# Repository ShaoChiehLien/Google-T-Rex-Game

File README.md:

# Google-T-Rex-Game
Introduction: We developed the Google T-Rex Game which could be played using our customized circuit board. The T-Rex needs to overcome the obstacles by jumping across the cactus or dodging the upcoming crow to keep itself alive. The project could be separated into three parts, main game program, sound generation, and hardware development. In order to display the User Interface, we developed our own library to cooperate with the two-screen Graphic LCD (64+64)x64. It should be noted that STM32f051r8t6 has relative small memories(64 Kbyte flash memory and 8 Kbyte of SRAM), so we mainly use for loop and bit map to reduce the memory usage.

For the main game part, we used our own algorithm to randomly produce three different characters: single cactus, cactus cluster and crow with random distances, which is a significant specialty of this project. By using non-visible simple squares to record the characters' position, we could track if the T-Rec touch the cactus or crow and determine if it is Game Over. At last, we added the bit map of each character on the non-visible simple square to finish the User Interface.

For the sound generation, we used the concept of Digital to Analog Conversion, Timer, and Direct Memory Access to generate certain voltage output. By generating a waveform using the analog output and calculate each note's frequency, we could then produce a sound wave of notes from C, D, E to A and B.

Last but not least, the customized printed circuit board is another specialty of this project. The development board is also acceptable for this project, but the wiring is really a pain in the ass, so we developed the circuit board and soldered the STM32f051r8t6 ourselves. The wiring map and PCB are all provided in the above file.

# Project Video Demostration
https://www.youtube.com/watch?v=Yxi9itDUQOI

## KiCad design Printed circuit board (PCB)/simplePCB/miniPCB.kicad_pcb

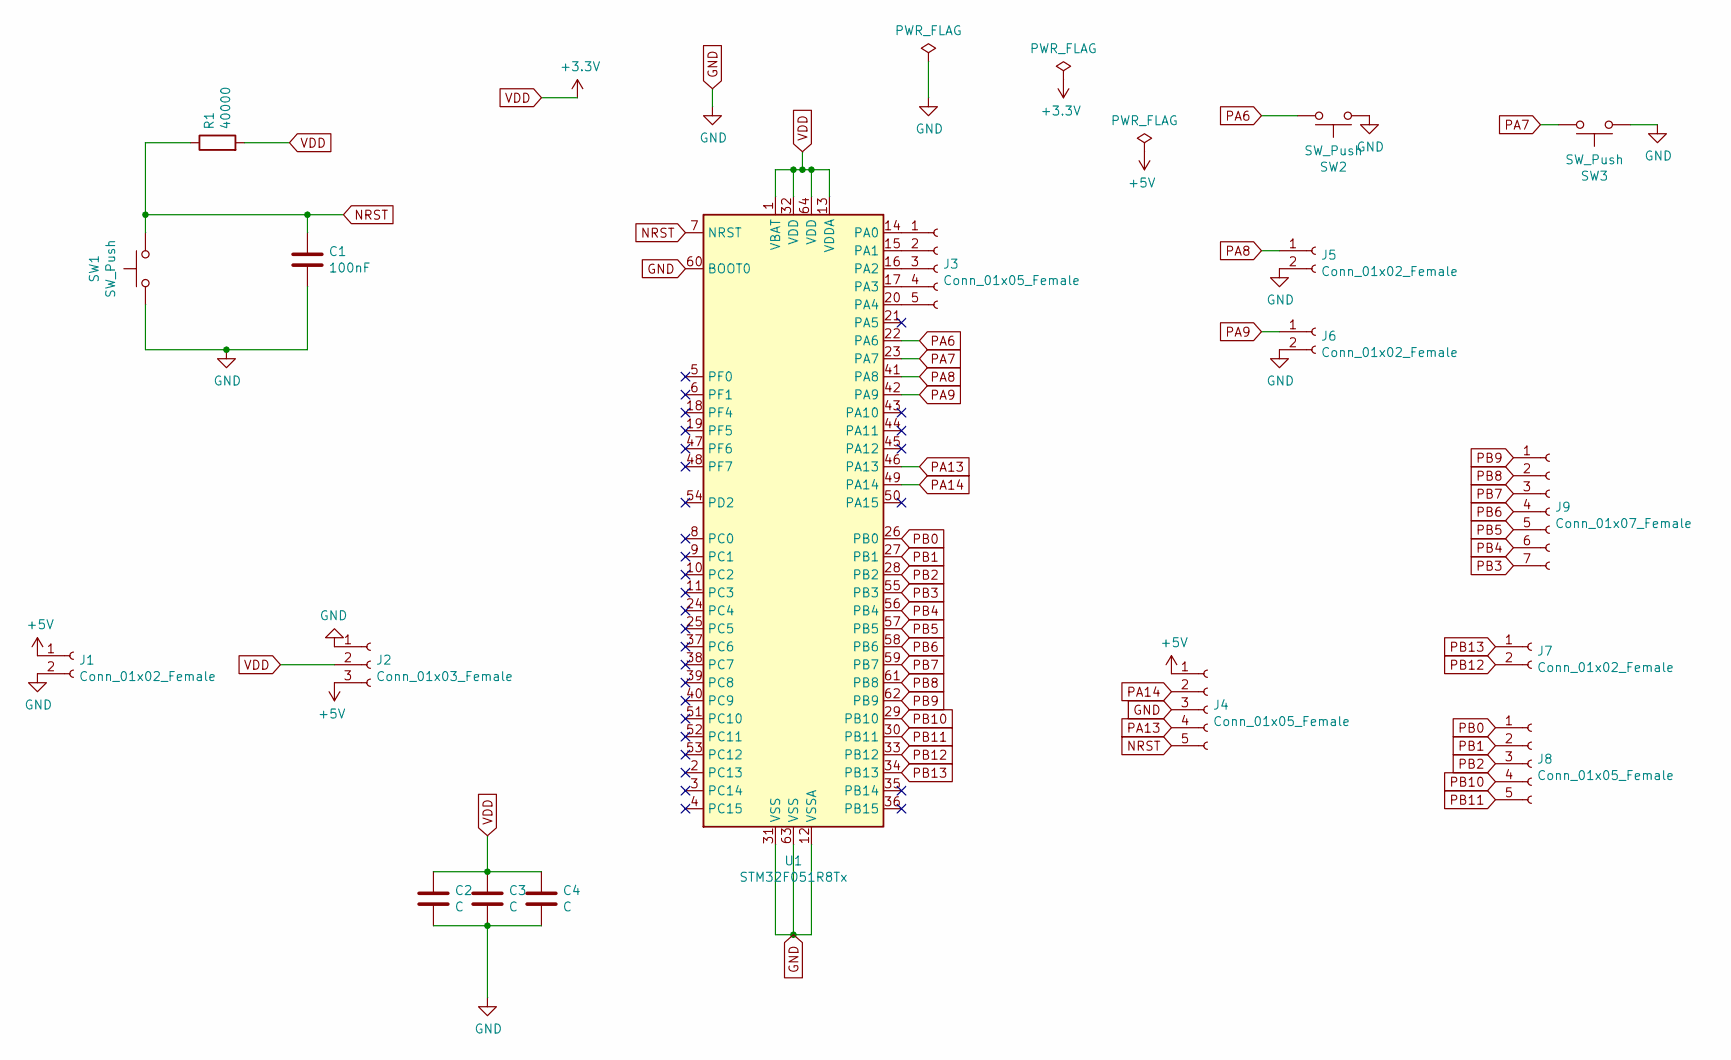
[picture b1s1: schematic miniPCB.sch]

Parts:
C1: 100nF; C_Axial_L3.8mm_D2.6mm_P7.50mm_Horizontal
C2, C3, C4: C; C_Radial_D6.3mm_H5.0mm_P2.50mm
J1, J5, J6, J7: Conn_01x02_Female; PinSocket_1x02_P2.54mm_Vertical
J2: Conn_01x03_Female; PinSocket_1x03_P2.54mm_Vertical
J3, J4, J8: Conn_01x05_Female; PinSocket_1x05_P2.54mm_Vertical
J9: Conn_01x07_Female; PinSocket_1x07_P2.54mm_Vertical
R1: 40000; R_Axial_DIN0207_L6.3mm_D2.5mm_P7.62mm_Horizontal
SW1, SW2, SW3: SW_Push; SW_Tactile_Straight_KSA0Axx1LFTR
U1: STM32F051R8Tx; LQFP-64_10x10mm_P0.5mm

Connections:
+5V: J1.1, J2.3, J4.1
GND: C1.2, C2.2, C3.2, C4.2, J1.2, J2.1, J4.3, J5.2, J6.2, SW1.1, SW2.1, SW3.1, U1.12 (VSSA), U1.31 (VSS), U1.60 (BOOT0), U1.63 (VSS)
NRST: C1.1, J4.5, R1.1, SW1.2, U1.7 (NRST)
unnamed: J3.1, U1.14 (PA0)
unnamed: J3.2, U1.15 (PA1)
unnamed: J3.3, U1.16 (PA2)
unnamed: J3.4, U1.17 (PA3)
unnamed: J3.5, U1.20 (PA4)
PA6: SW2.2, U1.22 (PA6)
PA7: SW3.2, U1.23 (PA7)
PA8: J5.1, U1.41 (PA8)
PA9: J6.1, U1.42 (PA9)
PA13: J4.4, U1.46 (PA13)
PA14: J4.2, U1.49 (PA14)
PB0: J8.1, U1.26 (PB0)
PB1: J8.2, U1.27 (PB1)
PB2: J8.3, U1.28 (PB2)
PB3: J9.7, U1.55 (PB3)
PB4: J9.6, U1.56 (PB4)
PB5: J9.5, U1.57 (PB5)
PB6: J9.4, U1.58 (PB6)
PB7: J9.3, U1.59 (PB7)
PB8: J9.2, U1.61 (PB8)
PB9: J9.1, U1.62 (PB9)
PB10: J8.4, U1.29 (PB10)
PB11: J8.5, U1.30 (PB11)
PB12: J7.2, U1.33 (PB12)
PB13: J7.1, U1.34 (PB13)
VDD: C2.1, C3.1, C4.1, J2.2, R1.2, U1.1 (VBAT), U1.13 (VDDA), U1.32 (VDD), U1.64 (VDD)

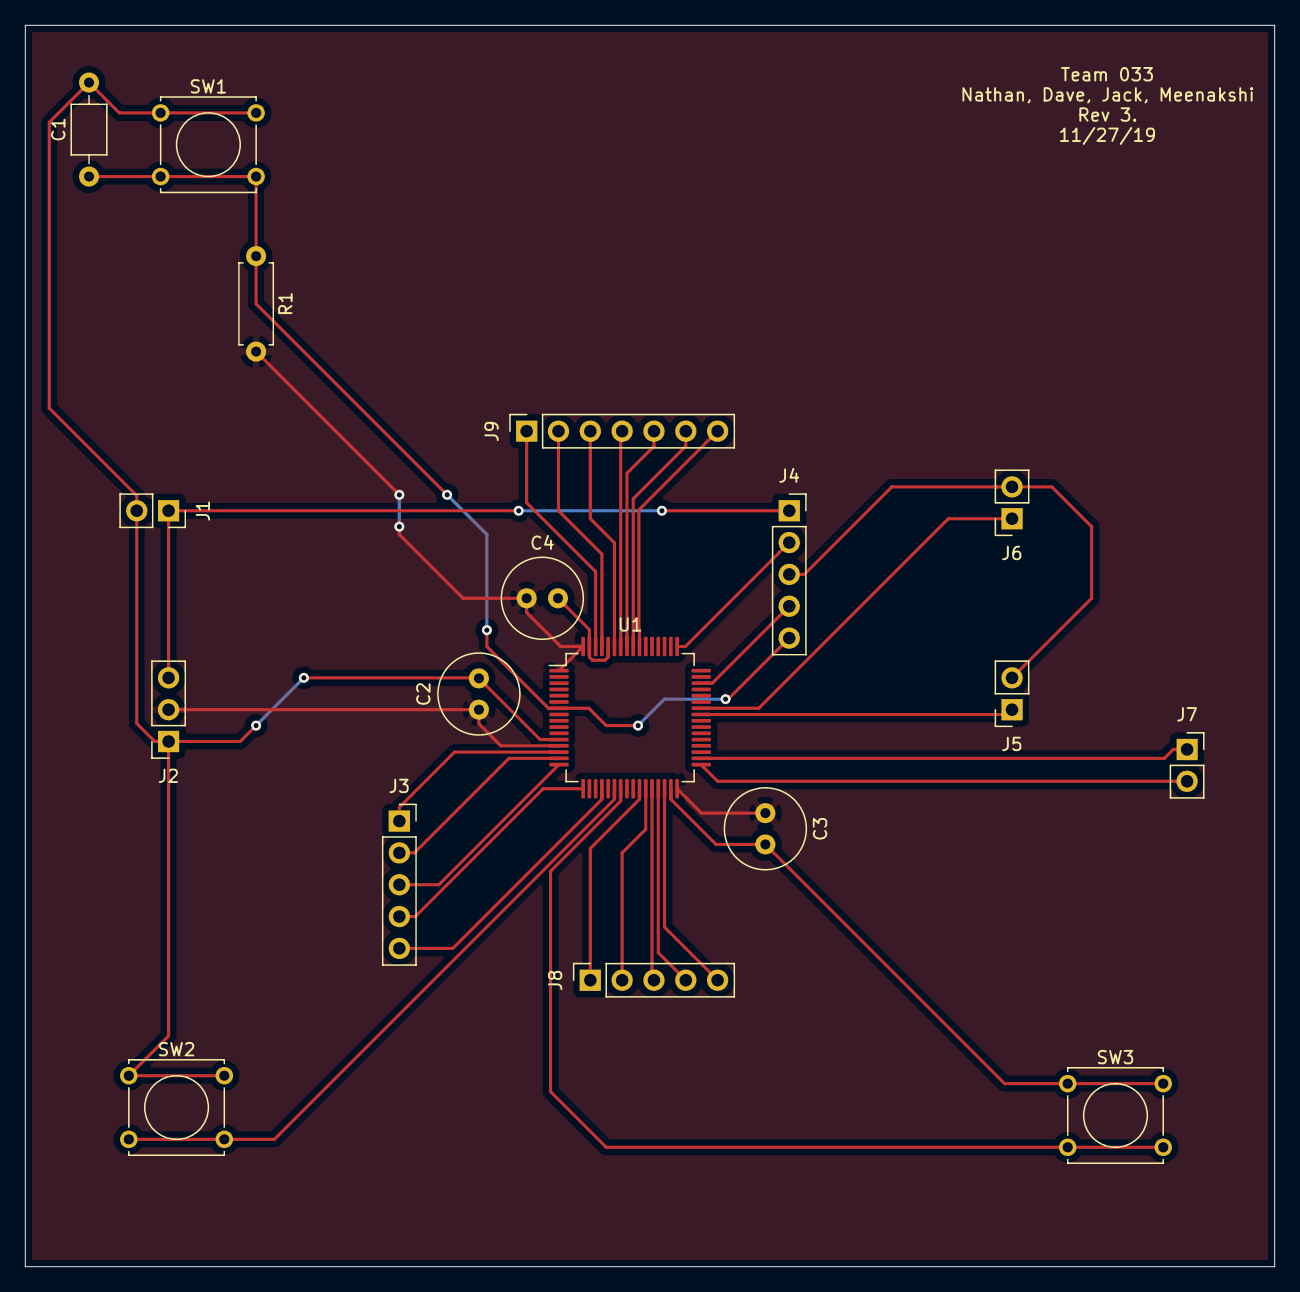
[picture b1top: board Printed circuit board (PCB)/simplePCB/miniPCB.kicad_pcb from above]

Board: 2 copper layers, 99.7 x 99.1 mm, 18 parts (0 on the bottom side), 29 nets.

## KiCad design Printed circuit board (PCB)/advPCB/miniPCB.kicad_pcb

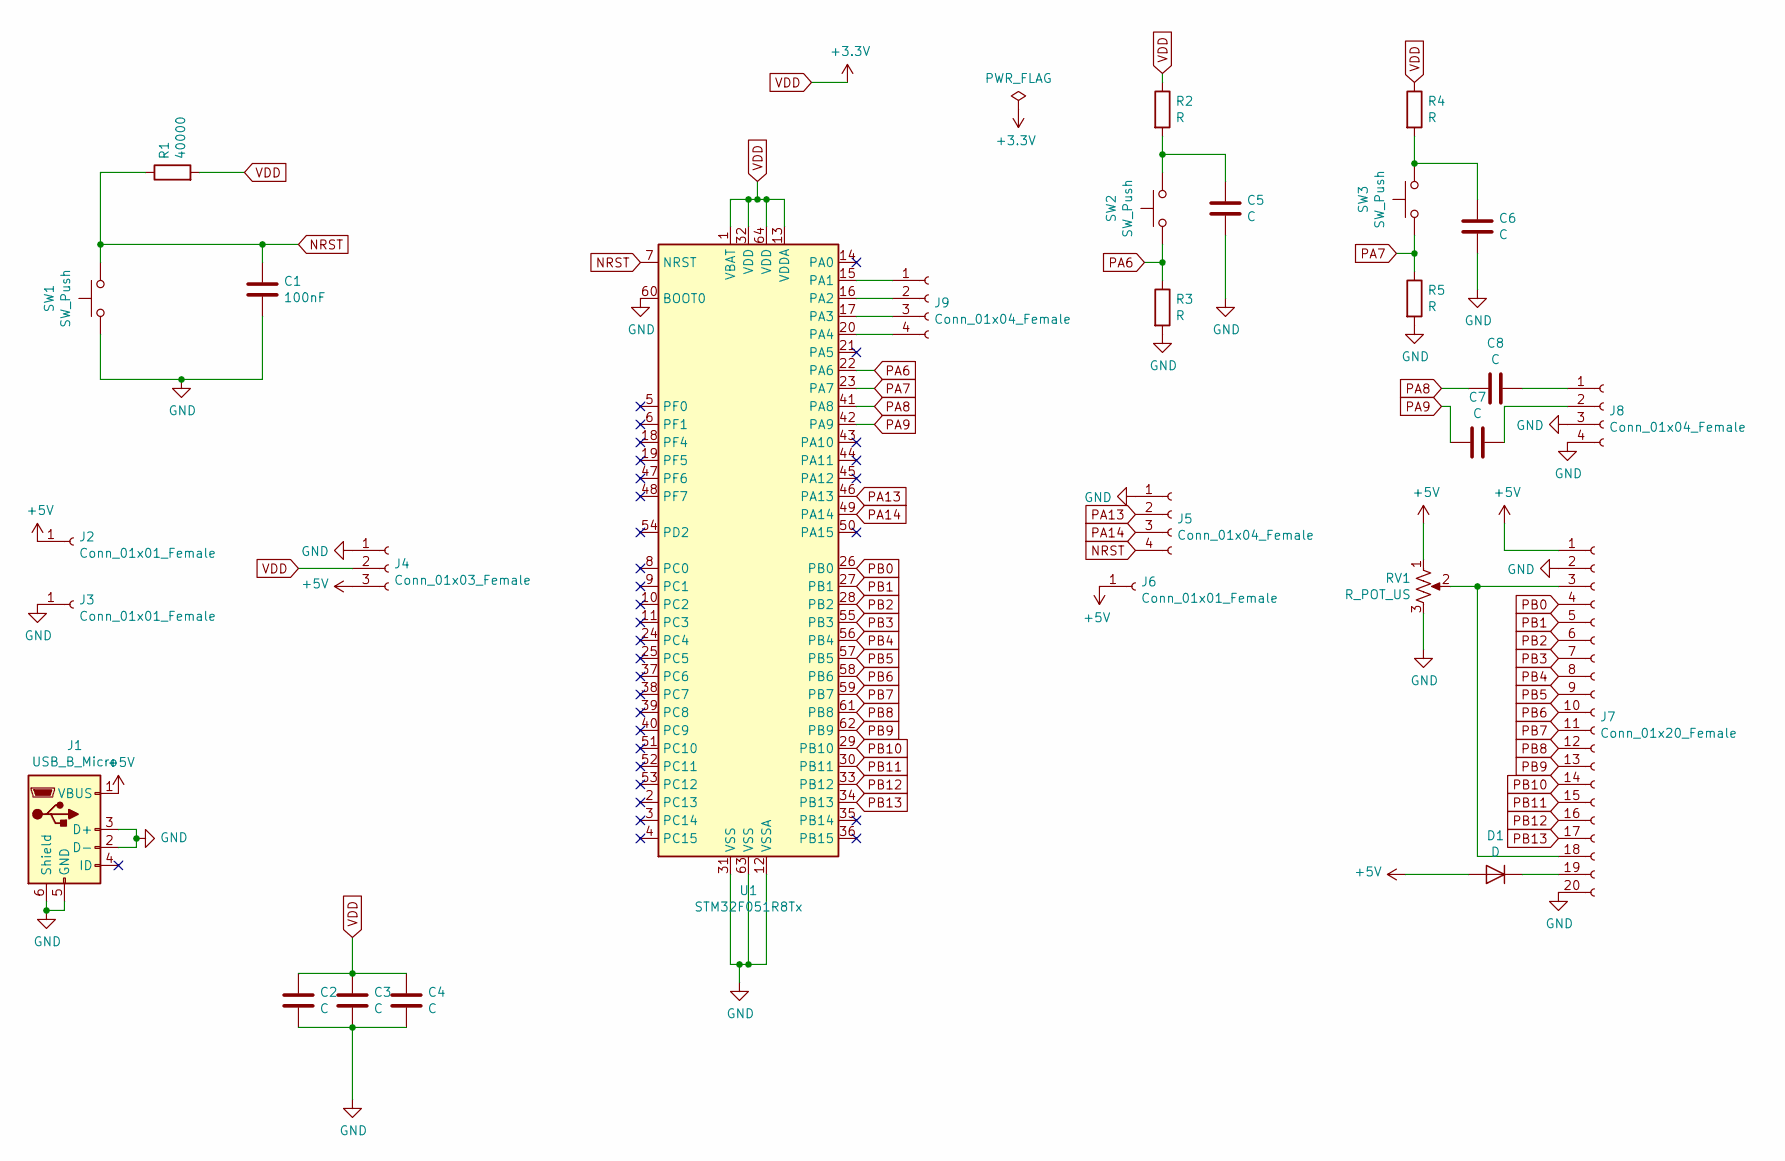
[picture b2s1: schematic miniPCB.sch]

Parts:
C1: 100nF; C_Axial_L3.8mm_D2.6mm_P7.50mm_Horizontal
C2, C3, C4: C; C_Radial_D6.3mm_H5.0mm_P2.50mm
C5, C6, C7, C8: C; C_Axial_L3.8mm_D2.6mm_P7.50mm_Horizontal
D1: D; D_5W_P10.16mm_Horizontal
J1: USB_B_Micro; USB_Micro-B_Molex_47346-0001
J2, J3, J6: Conn_01x01_Female; PinSocket_1x01_P2.54mm_Vertical
J4: Conn_01x03_Female; PinSocket_1x03_P2.54mm_Vertical
J5, J8, J9: Conn_01x04_Female; PinSocket_1x04_P2.54mm_Vertical
J7: Conn_01x20_Female; PinSocket_1x20_P2.54mm_Vertical
R1: 40000; R_Axial_DIN0207_L6.3mm_D2.5mm_P7.62mm_Horizontal
R2, R3, R4, R5: R; R_Axial_DIN0207_L6.3mm_D2.5mm_P7.62mm_Horizontal
RV1: R_POT_US; Potentiometer_Alps_RK09K_Single_Vertical
SW1, SW2, SW3: SW_Push; SW_Tactile_Straight_KSA0Axx1LFTR
U1: STM32F051R8Tx; LQFP-64_10x10mm_P0.5mm

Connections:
+5V: D1.2 (A), J1.1 (VBUS), J2.1, J4.3, J6.1, J7.1, RV1.1
GND: C1.2, C2.2, C3.2, C4.2, C5.2, C6.2, J1.2 (D-), J1.3 (D+), J1.5 (GND), J1.6 (Shield), J3.1, J4.1, J5.1, J7.2, J7.20, J8.3, J8.4, R3.2, R5.2, RV1.3, SW1.1, U1.12 (VSSA), U1.31 (VSS), U1.60 (BOOT0), U1.63 (VSS)
NRST: C1.1, J5.4, R1.1, SW1.2, U1.7 (NRST)
unnamed: C5.1, R2.2, SW2.2
unnamed: C6.1, R4.2, SW3.2
unnamed: C7.1, J8.2
unnamed: C8.1, J8.1
unnamed: D1.1 (K), J7.19
unnamed: J7.3, J7.18, RV1.2
unnamed: J9.1, U1.15 (PA1)
unnamed: J9.2, U1.16 (PA2)
unnamed: J9.3, U1.17 (PA3)
unnamed: J9.4, U1.20 (PA4)
PA6: R3.1, SW2.1, U1.22 (PA6)
PA7: R5.1, SW3.1, U1.23 (PA7)
PA8: C8.2, U1.41 (PA8)
PA9: C7.2, U1.42 (PA9)
PA13: J5.2, U1.46 (PA13)
PA14: J5.3, U1.49 (PA14)
PB0: J7.4, U1.26 (PB0)
PB1: J7.5, U1.27 (PB1)
PB2: J7.6, U1.28 (PB2)
PB3: J7.7, U1.55 (PB3)
PB4: J7.8, U1.56 (PB4)
PB5: J7.9, U1.57 (PB5)
PB6: J7.10, U1.58 (PB6)
PB7: J7.11, U1.59 (PB7)
PB8: J7.12, U1.61 (PB8)
PB9: J7.13, U1.62 (PB9)
PB10: J7.14, U1.29 (PB10)
PB11: J7.15, U1.30 (PB11)
PB12: J7.16, U1.33 (PB12)
PB13: J7.17, U1.34 (PB13)
VDD: C2.1, C3.1, C4.1, J4.2, R1.2, R2.1, R4.1, U1.1 (VBAT), U1.13 (VDDA), U1.32 (VDD), U1.64 (VDD)

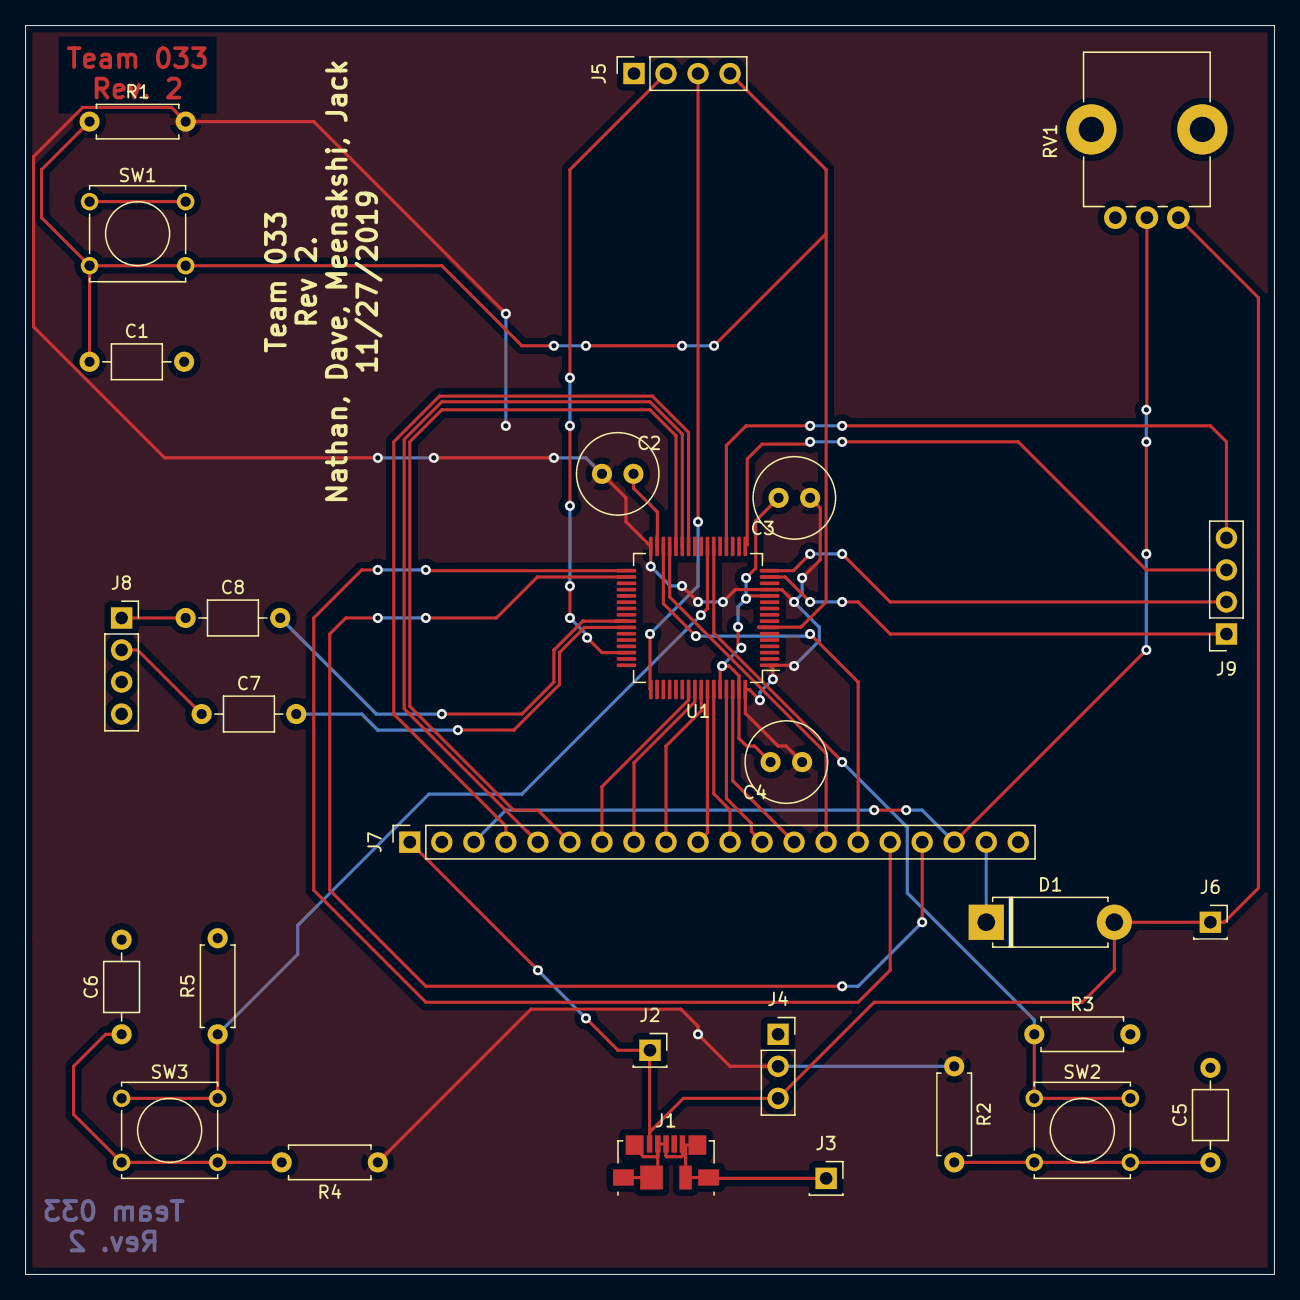
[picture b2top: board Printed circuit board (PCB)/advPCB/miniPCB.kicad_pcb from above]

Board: 2 copper layers, 99.1 x 99.1 mm, 28 parts (0 on the bottom side), 34 nets.

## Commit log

2020-01-05 Upload File
